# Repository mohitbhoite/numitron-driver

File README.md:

# numitron-driver
Display driver for the numitron 7 segment display tube based on the MAX7313

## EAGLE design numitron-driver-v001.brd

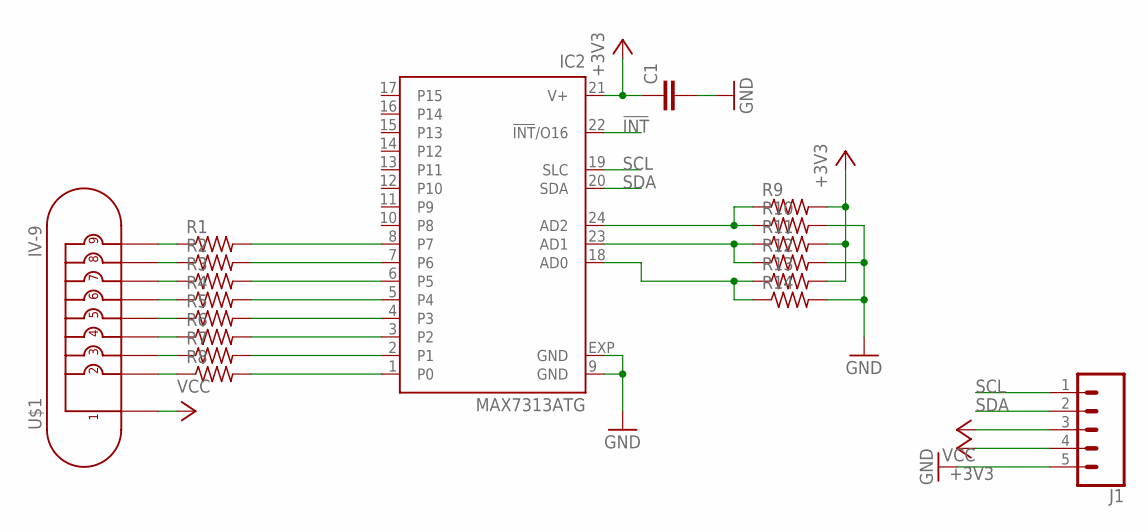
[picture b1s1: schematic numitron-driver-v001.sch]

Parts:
C1: C-EUC0603; C0603
IC2: MAX7313ATG; TQFN24-EP
J1: CONN_05NO_SILK; 1X05_NO_SILK
R1, R2, R3, R4, R5, R6, R7, R8: R-US_R0603; R0603
R9, R10, R11, R12, R13, R14: R-US_R0402; R0402
U$1: IV-9

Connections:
!INT: IC2.22 (!INT!/O16)
+3V3: C1.1, IC2.21 (V+), J1.4, R9.2, R11.2, R13.2
GND: C1.2, IC2.9 (GND), IC2.EXP (GND), J1.5, R10.2, R12.2, R14.2
unnamed: R1.1, U$1.9
unnamed: R2.1, U$1.8
unnamed: R3.1, U$1.7
unnamed: R4.1, U$1.6
unnamed: R5.1, U$1.5
unnamed: R6.1, U$1.4
unnamed: R7.1, U$1.3
unnamed: R8.1, U$1.2
unnamed: IC2.1 (P0), R8.2
unnamed: IC2.2 (P1), R7.2
unnamed: IC2.3 (P2), R6.2
unnamed: IC2.4 (P3), R5.2
unnamed: IC2.5 (P4), R4.2
unnamed: IC2.6 (P5), R3.2
unnamed: IC2.7 (P6), R2.2
unnamed: IC2.8 (P7), R1.2
unnamed: IC2.18 (AD0), R13.1, R14.1
unnamed: IC2.23 (AD1), R11.1, R12.1
unnamed: IC2.24 (AD2), R9.1, R10.1
SCL: IC2.19 (SLC), J1.1
SDA: IC2.20 (SDA), J1.2
VCC: J1.3, U$1.1

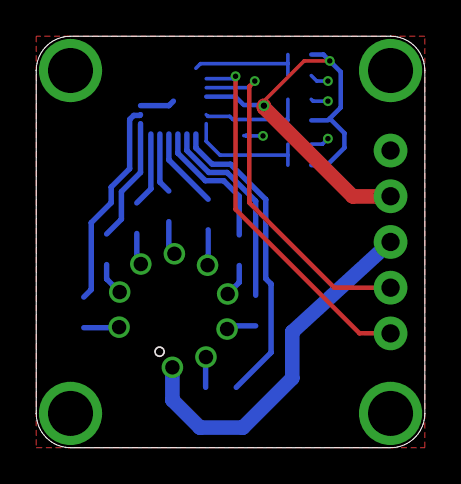
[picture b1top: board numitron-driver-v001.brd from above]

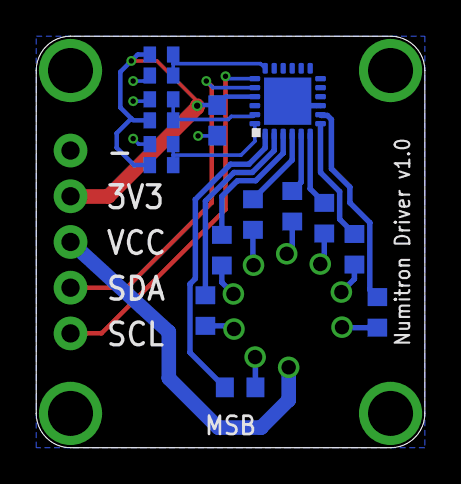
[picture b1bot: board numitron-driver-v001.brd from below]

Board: 2 copper layers, 21.6 x 22.9 mm, 18 parts (16 on the bottom side), 24 nets.

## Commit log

2019-02-19 added design files

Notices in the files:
parts and their libraries:
SparkFun-Connectors: Licensing: Creative Commons ShareAlike 4.0 International - https://creativecommons.org/licenses/by-sa/4.0
